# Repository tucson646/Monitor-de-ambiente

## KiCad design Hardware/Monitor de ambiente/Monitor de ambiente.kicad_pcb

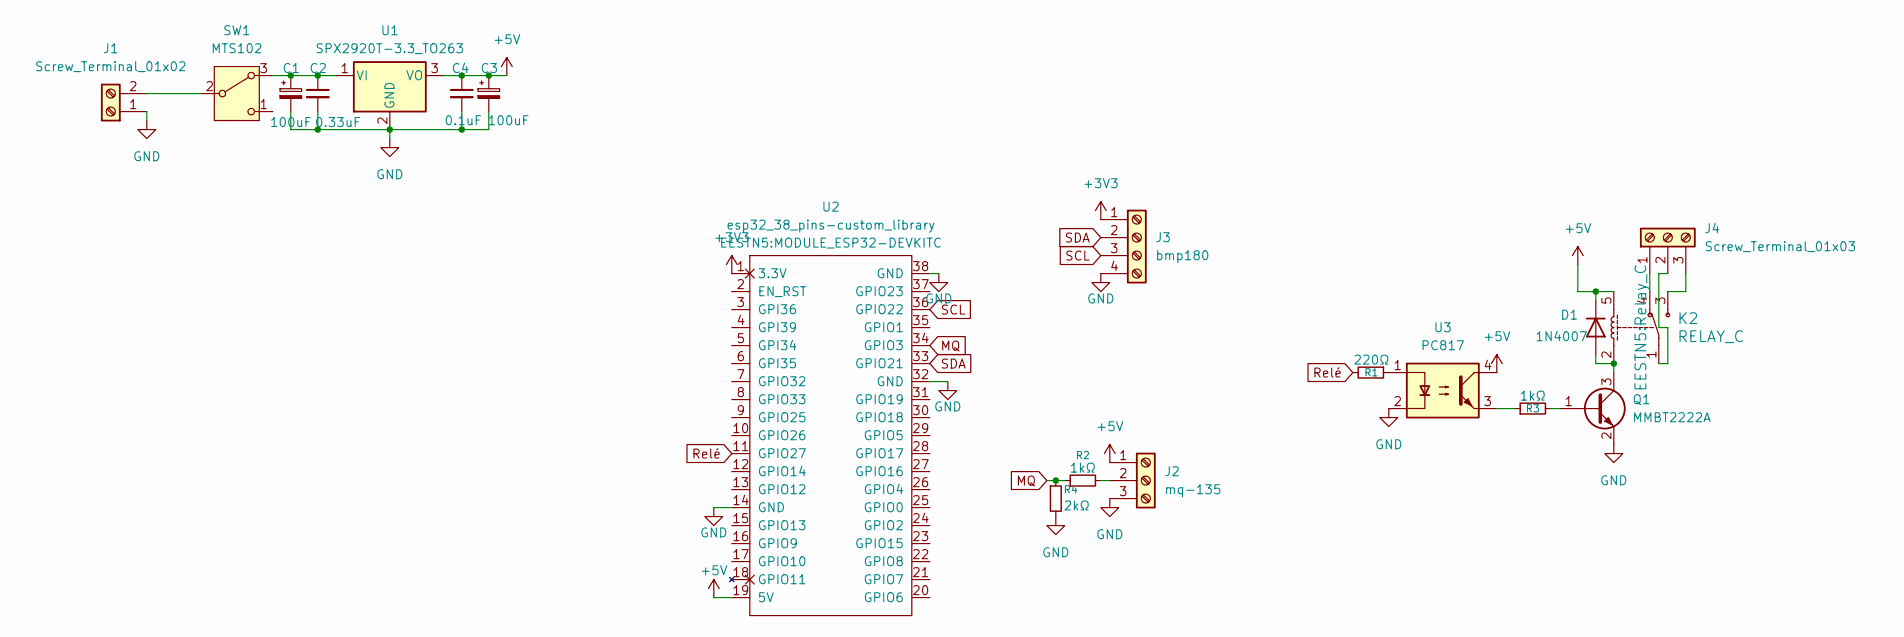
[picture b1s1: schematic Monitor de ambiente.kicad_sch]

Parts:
C1, C3: 100uF; CAP_ELEC_5x11mm
C2: 0.33uF; CAP_0.2
C4: 0.1uF; CAP_0.2
D1: 1N4007; D_1206_3216Metric
J1: Screw_Terminal_01x02; AMASS_XT30U-F_1x02_P5.0mm_Vertical
J2: mq-135; PinHeader_1x03_P2.54mm_Vertical
J3: bmp180; PinHeader_1x04_P2.54mm_Vertical
J4: Screw_Terminal_01x03; TerminalBlock_Phoenix_MKDS-1,5-3_1x03_P5.00mm_Horizontal
K2: RELAY_C; Relay_C
Q1: MMBT2222A; SOT-23
R1: 220Ω; R_0805_2012Metric_Pad1.20x1.40mm_HandSolder
R2, R3: 1kΩ; R_0805_2012Metric_Pad1.20x1.40mm_HandSolder
R4: 2kΩ; R_0805_2012Metric_Pad1.20x1.40mm_HandSolder
SW1: MTS102; SW_SPDT_TH_Vertical
U1: SPX2920T-3.3_TO263; TO-263-2
U2: esp32_38_pins-custom_library; MODULE_ESP32-DEVKITC
U3: PC817; DIP-4_W7.62mm

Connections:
+3V3: J3.1, U2.1 (3.3V)
+5V: C3.1, C4.1, D1.1 (K), J2.1, K2.5, U1.3 (VO), U2.19 (5V), U3.4
GND: C1.2, C2.2, C3.2, C4.2, J1.1, J2.3, J3.4, Q1.2 (E), R4.2, U1.2 (GND), U2.14 (GND), U2.32 (GND), U2.38 (GND), U3.2
MQ: R2.1, R4.1, U2.34 (GPIO3)
unnamed: D1.2 (A), K2.2, Q1.3 (C)
unnamed: J1.2, SW1.2 (B)
unnamed: J2.2, R2.2
unnamed: J4.1, K2.4
unnamed: J4.2, K2.1
unnamed: J4.3, K2.3
unnamed: Q1.1 (B), R3.2
unnamed: R1.1, U3.1
unnamed: R3.1, U3.3
unnamed: C1.1, C2.1, SW1.3 (A), U1.1 (VI)
Relé: R1.2, U2.11 (GPIO27)
SCL: J3.3, U2.36 (GPIO22)
SDA: J3.2, U2.33 (GPIO21)

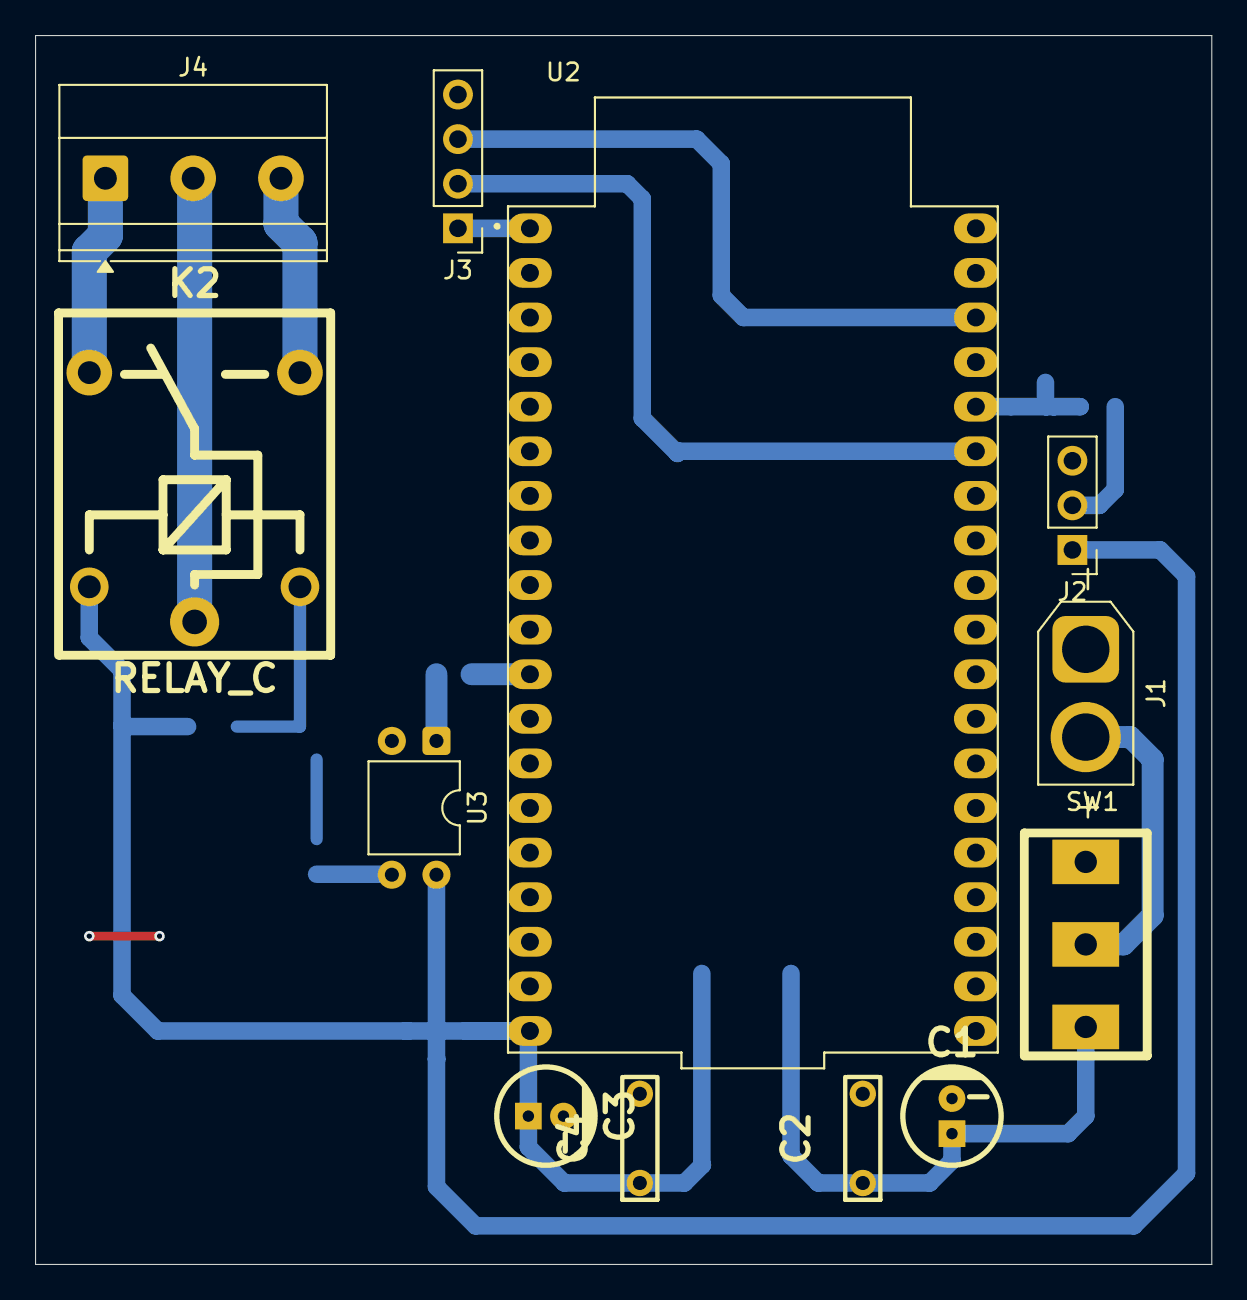
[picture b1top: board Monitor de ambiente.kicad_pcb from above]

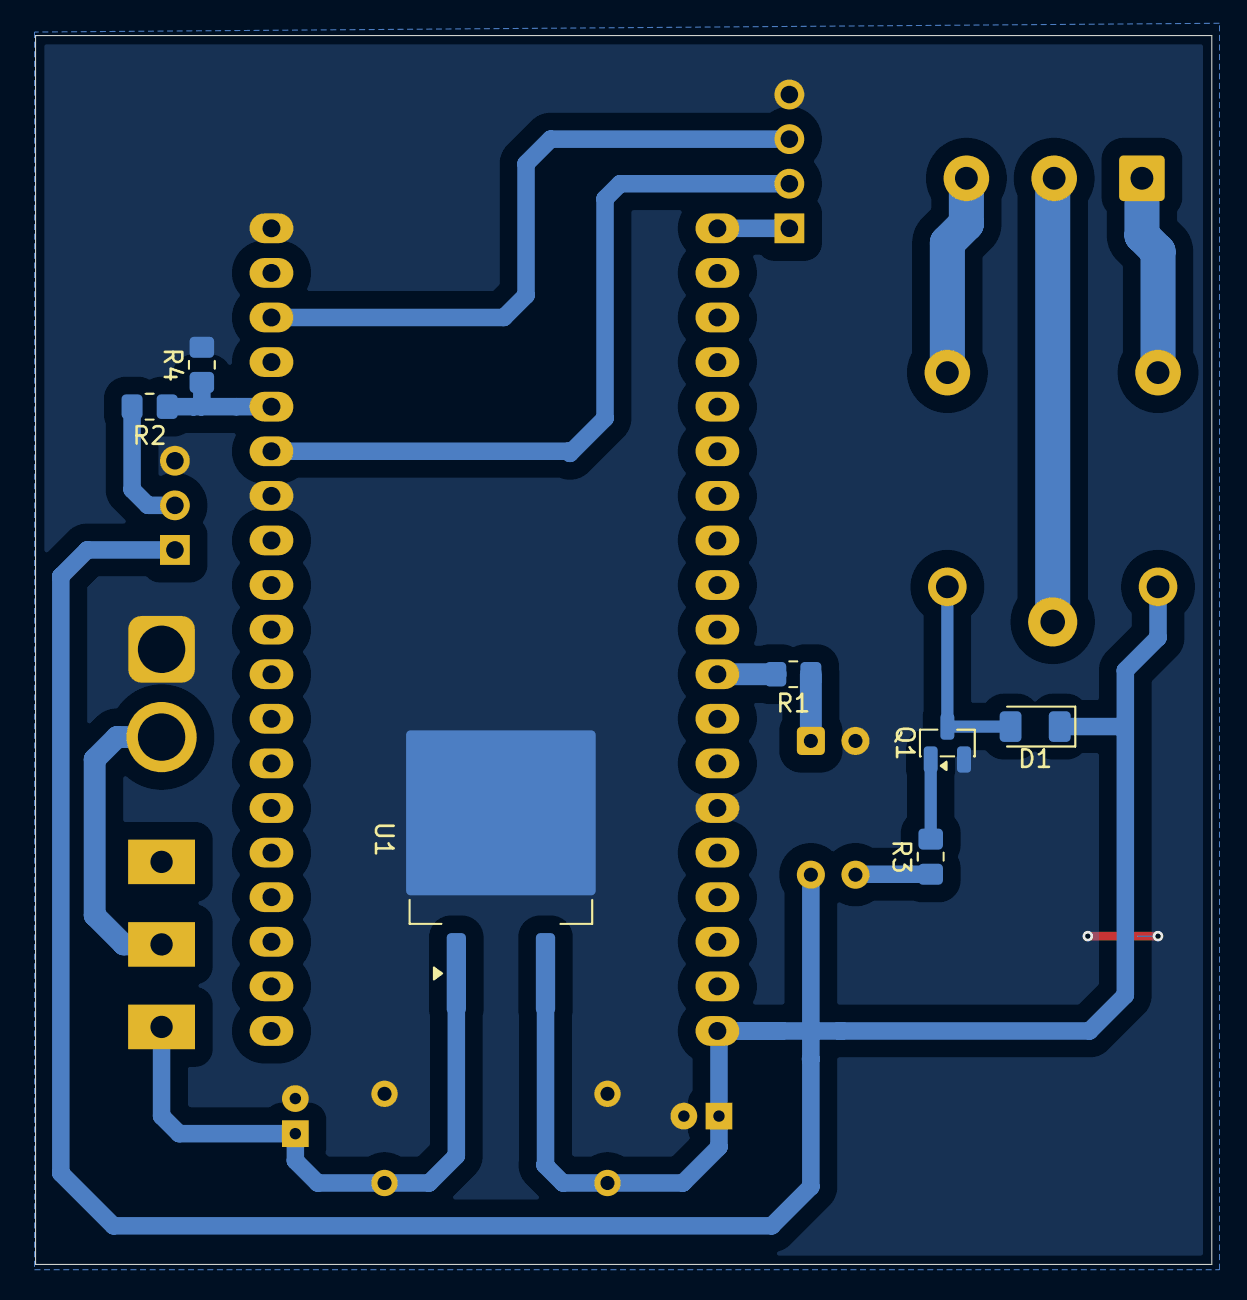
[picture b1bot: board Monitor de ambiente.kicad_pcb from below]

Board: 2 copper layers, 67.0 x 70.0 mm, 19 parts (7 on the bottom side), 17 nets.
